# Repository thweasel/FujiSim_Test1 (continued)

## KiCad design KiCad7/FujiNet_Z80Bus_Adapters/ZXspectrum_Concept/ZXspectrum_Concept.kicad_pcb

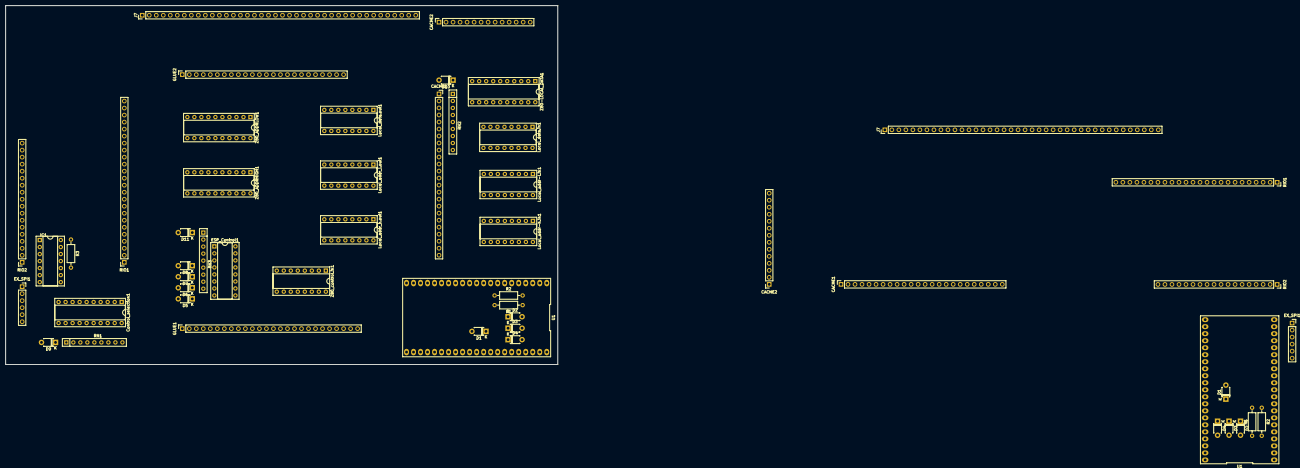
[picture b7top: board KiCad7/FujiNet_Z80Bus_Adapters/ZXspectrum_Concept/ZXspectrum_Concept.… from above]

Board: 2 copper layers, 200.0 x 130.0 mm, 52 parts (0 on the bottom side), 130 nets, no tracks yet.

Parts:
CACHE1, CACHE1#2: Conn_01x24_Socket; PinSocket_1x24_P2.54mm_Vertical
CACHE2, CACHE2#2: Conn_01x14_Socket; PinSocket_1x14_P2.54mm_Vertical
Control_selection1: 74HC244N; DIP-20_W7.62mm_Socket
D1, D1#2, D2, D2#2, D3, D3#2, D4, D4#2, D5, D6, D7, D8, D9, D10, D11: 1N4148; D_T-1_P5.08mm_Horizontal
ESP_Control1: 74595N; DIP-16_W7.62mm_Socket
EX_SPI1, EX_SPI1#2: PinSocket_2.54mm; PinSocket_1x06_P2.54mm_Vertical
GLUE1: Conn_01x26_Socket; PinSocket_1x26_P2.54mm_Vertical
GLUE2: Conn_01x24_Socket; PinSocket_1x24_P2.54mm_Vertical
IC1: 74HC32N; DIP-14_W7.62mm_Socket
J7, J7#2: DIAG-HOST_SYSTEM_BUS; PinHeader_1x40_P2.54mm_Vertical
Local_addr-h.in1: 74HC165N; DIP-16_W7.62mm_Socket
Local_addr-l.in1: 74HC165N; DIP-16_W7.62mm_Socket
Local_addr_h.out1: 74595N; DIP-16_W7.62mm_Socket
Local_addr_l.out1: 74595N; DIP-16_W7.62mm_Socket
Local_data.in1: 74HC165N; DIP-16_W7.62mm_Socket
Local_data.out1: 74595N; DIP-16_W7.62mm_Socket
R1, R1#2, R2, R2#2, R3: 22K; R_Axial_DIN0207_L6.3mm_D2.5mm_P10.16mm_Horizontal
RIO1, RIO1#2: Conn_01x24_Socket; PinSocket_1x24_P2.54mm_Vertical
RIO2, RIO2#2: Conn_01x18_Socket; PinSocket_1x18_P2.54mm_Vertical
RN1: LOCAL_CONTROL_BIAS; R_Array_SIP9
RN2, RN3: 4609M-101-103LF; R_Array_SIP9
U1, U1#2: FREENOVE_ESP32-WROVER-DEV
Z80-LOCAL_DATA1, Z80_ADDRHIGH1, Z80_ADDRLOW1: 74HC245N; DIP-20_W7.62mm_Socket
Z80_control.in1: 74HC165N; DIP-16_W7.62mm_Socket

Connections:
+5V: CACHE2.1, CACHE2#2.1, Control_selection1.20 (VCC), D9.2 (A), D10.2 (A), D11.2 (A), ESP_Control1.16 (VCC), EX_SPI1.5, GLUE1.1, IC1.14 (VCC), Local_addr-h.in1.16 (VCC), Local_addr-l.in1.16 (VCC), Local_addr_h.out1.16 (VCC), Local_addr_l.out1.16 (VCC), Local_data.in1.16 (VCC), Local_data.out1.16 (VCC), R1.2, R1#2.2, R3.1, RIO2.1, RIO2#2.1, U1.20 (+5V), U1#2.20 (+5V), Z80-LOCAL_DATA1.20 (VCC), Z80_ADDRHIGH1.20 (VCC), Z80_ADDRLOW1.20 (VCC), Z80_control.in1.16 (VCC)
/CACHE connector/CACHE_CONTROL.A16: CACHE2.2, CACHE2#2.2, GLUE2.14
/CACHE connector/CACHE_CONTROL.CS: CACHE2.5, CACHE2#2.5, GLUE2.17
/CACHE connector/CACHE_CONTROL.DATASTATUS+PERM_Z80_IORQ: CACHE2.6, CACHE2#2.6, GLUE2.13
/CACHE connector/CACHE_CONTROL.OE: CACHE2.4, CACHE2#2.4, GLUE2.16
/CACHE connector/CACHE_CONTROL.WE: CACHE2.3, CACHE2#2.3, GLUE2.15
/CACHE connector/CACHE_DATASTATUS: CACHE2.12, CACHE2#2.12, GLUE2.5, RIO2.13, RIO2#2.13
/CACHE connector/CACHE_SEL_0: CACHE2.8, CACHE2#2.8, RIO2.9, RIO2#2.9
/CACHE connector/CACHE_SEL_1: CACHE2.9, CACHE2#2.9, RIO2.10, RIO2#2.10
/CACHE connector/CACHE_SEL_2: CACHE2.10, CACHE2#2.10, RIO2.11, RIO2#2.11
/CACHE connector/CACHE_SEL_3: CACHE2.11, CACHE2#2.11, RIO2.12, RIO2#2.12
/CACHE connector/LOCAL_A0: CACHE1.9, CACHE1#2.9, Local_addr-l.in1.11 (D0), Local_addr_l.out1.15 (QA), Z80_ADDRLOW1.18 (B0)
/CACHE connector/LOCAL_A1: CACHE1.10, CACHE1#2.10, Local_addr-l.in1.12 (D1), Local_addr_l.out1.1 (QB), Z80_ADDRLOW1.17 (B1)
/CACHE connector/LOCAL_A2: CACHE1.11, CACHE1#2.11, Local_addr-l.in1.13 (D2), Local_addr_l.out1.2 (QC), Z80_ADDRLOW1.16 (B2)
/CACHE connector/LOCAL_A3: CACHE1.12, CACHE1#2.12, Local_addr-l.in1.14 (D3), Local_addr_l.out1.3 (QD), Z80_ADDRLOW1.15 (B3)
/CACHE connector/LOCAL_A4: CACHE1.13, CACHE1#2.13, Local_addr-l.in1.3 (D4), Local_addr_l.out1.4 (QE), Z80_ADDRLOW1.14 (B4)
/CACHE connector/LOCAL_A5: CACHE1.14, CACHE1#2.14, Local_addr-l.in1.4 (D5), Local_addr_l.out1.5 (QF), Z80_ADDRLOW1.13 (B5)
/CACHE connector/LOCAL_A6: CACHE1.15, CACHE1#2.15, Local_addr-l.in1.5 (D6), Local_addr_l.out1.6 (QG), Z80_ADDRLOW1.12 (B6)
/CACHE connector/LOCAL_A7: CACHE1.16, CACHE1#2.16, Local_addr-l.in1.6 (D7), Local_addr_l.out1.7 (QH), Z80_ADDRLOW1.11 (B7)
/CACHE connector/LOCAL_A8: CACHE1.17, CACHE1#2.17, Local_addr-h.in1.11 (D0), Local_addr_h.out1.15 (QA), Z80_ADDRHIGH1.18 (B0)
/CACHE connector/LOCAL_A9: CACHE1.18, CACHE1#2.18, Local_addr-h.in1.12 (D1), Local_addr_h.out1.1 (QB), Z80_ADDRHIGH1.17 (B1)
/CACHE connector/LOCAL_A10: CACHE1.19, CACHE1#2.19, Local_addr-h.in1.13 (D2), Local_addr_h.out1.2 (QC), Z80_ADDRHIGH1.16 (B2)
/CACHE connector/LOCAL_A11: CACHE1.20, CACHE1#2.20, Local_addr-h.in1.14 (D3), Local_addr_h.out1.3 (QD), Z80_ADDRHIGH1.15 (B3)
/CACHE connector/LOCAL_A12: CACHE1.21, CACHE1#2.21, Local_addr-h.in1.3 (D4), Local_addr_h.out1.4 (QE), Z80_ADDRHIGH1.14 (B4)
/CACHE connector/LOCAL_A13: CACHE1.22, CACHE1#2.22, Local_addr-h.in1.4 (D5), Local_addr_h.out1.5 (QF), Z80_ADDRHIGH1.13 (B5)
/CACHE connector/LOCAL_A14: CACHE1.23, CACHE1#2.23, Local_addr-h.in1.5 (D6), Local_addr_h.out1.6 (QG), Z80_ADDRHIGH1.12 (B6)
/CACHE connector/LOCAL_A15: CACHE1.24, CACHE1#2.24, Local_addr-h.in1.6 (D7), Local_addr_h.out1.7 (QH), Z80_ADDRHIGH1.11 (B7)
/CACHE connector/LOCAL_D0: CACHE1.1, CACHE1#2.1, Local_data.in1.11 (D0), Local_data.out1.15 (QA), RN2.2 (R1), Z80-LOCAL_DATA1.18 (B0)
/CACHE connector/LOCAL_D1: CACHE1.2, CACHE1#2.2, Local_data.in1.12 (D1), Local_data.out1.1 (QB), RN2.3 (R2), Z80-LOCAL_DATA1.17 (B1)
/CACHE connector/LOCAL_D2: CACHE1.3, CACHE1#2.3, Local_data.in1.13 (D2), Local_data.out1.2 (QC), RN2.4 (R3), Z80-LOCAL_DATA1.16 (B2)
/CACHE connector/LOCAL_D3: CACHE1.4, CACHE1#2.4, Local_data.in1.14 (D3), Local_data.out1.3 (QD), RN2.5 (R4), Z80-LOCAL_DATA1.15 (B3)
/CACHE connector/LOCAL_D4: CACHE1.5, CACHE1#2.5, Local_data.in1.3 (D4), Local_data.out1.4 (QE), RN2.6 (R5), Z80-LOCAL_DATA1.14 (B4)
/CACHE connector/LOCAL_D5: CACHE1.6, CACHE1#2.6, Local_data.in1.4 (D5), Local_data.out1.5 (QF), RN2.7 (R6), Z80-LOCAL_DATA1.13 (B5)
/CACHE connector/LOCAL_D6: CACHE1.7, CACHE1#2.7, Local_data.in1.5 (D6), Local_data.out1.6 (QG), RN2.8 (R7), Z80-LOCAL_DATA1.12 (B6)
/CACHE connector/LOCAL_D7: CACHE1.8, CACHE1#2.8, Local_data.in1.6 (D7), Local_data.out1.7 (QH), RN2.9 (R8), Z80-LOCAL_DATA1.11 (B7)
/CACHE connector/Z80_HARDLOCK: CACHE2.7, CACHE2#2.7, GLUE1.22, U1.4 (GPIO39), U1#2.4 (GPIO39)
/CORE/ESP_HARDLOCK: GLUE1.20, U1.26 (GPIO2), U1#2.26 (GPIO2)
/CORE/ESP_INT: D2.2 (A), D2#2.2 (A), D3.2 (A), D3#2.2 (A), D4.2 (A), D4#2.2 (A), R1.1, R1#2.1, R2.2, R2#2.2, U1.3 (GPIO36), U1#2.3 (GPIO36)
/CORE/ESP_PULSE: IC1.1, U1.11 (GPIO27), U1#2.11 (GPIO27)
/CORE/ESP_ROMSEL_0: GLUE1.18, U1.23 (GPIO7), U1#2.23 (GPIO7)
/CORE/ESP_ROMSEL_1: GLUE1.19, U1.22 (GPIO6), U1#2.22 (GPIO6)
/CORE/ESP_ROM_WR_PROTECT: GLUE1.17, U1.28 (GPIO4), U1#2.28 (GPIO4)
/CORE/ESP_SPI_INT.CE: Local_addr-h.in1.15 (~CE), Local_addr-l.in1.15 (~CE), Local_data.in1.15 (~CE), U1.31 (GPIO5), U1#2.31 (GPIO5), Z80_control.in1.15 (~CE)
/CORE/ESP_SPI_INT.MISO: Local_addr-h.in1.7 (~Q7), U1.33 (GPIO19), U1#2.33 (GPIO19)
/CORE/ESP_SPI_INT.MOSI: Local_data.out1.14 (SER), U1.39 (GPIO23), U1#2.39 (GPIO23)
/CORE/ESP_SPI_INT.MR: ESP_Control1.10 (~SRCLR), Local_addr_h.out1.10 (~SRCLR), Local_addr_l.out1.10 (~SRCLR), Local_data.out1.10 (~SRCLR), R3.2
/CORE/ESP_SPI_INT.OE: ESP_Control1.13 (~OE), Local_addr_h.out1.13 (~OE), Local_addr_l.out1.13 (~OE), U1.8 (GPIO33), U1#2.8 (GPIO33)
/CORE/ESP_SPI_INT.PL: Local_addr-h.in1.1 (~PL), Local_addr-l.in1.1 (~PL), Local_data.in1.1 (~PL), U1.9 (GPIO25), U1#2.9 (GPIO25), Z80_control.in1.1 (~PL)
/CORE/ESP_SPI_INT.SCK: ESP_Control1.11 (SRCLK), Local_addr-h.in1.2 (CP), Local_addr-l.in1.2 (CP), Local_addr_h.out1.11 (SRCLK), Local_addr_l.out1.11 (SRCLK), Local_data.in1.2 (CP), Local_data.out1.11 (SRCLK), U1.32 (GPIO18), U1#2.32 (GPIO18), Z80_control.in1.2 (CP)
/CORE/ESP_SPI_INT.STC: ESP_Control1.12 (RCLK), Local_addr_h.out1.12 (RCLK), Local_addr_l.out1.12 (RCLK), Local_data.out1.12 (RCLK), U1.10 (GPIO26), U1#2.10 (GPIO26)
/CORE/ESP_WAIT_RESET: GLUE2.6, U1.18 (GPIO11), U1#2.18 (GPIO11)
/CORE/EX_MISO: EX_SPI1.3, U1.13 (GPIO12), U1#2.13 (GPIO12)
/CORE/EX_MOSI: EX_SPI1.4, U1.15 (GPIO13), U1#2.15 (GPIO13)
/CORE/EX_SCK: EX_SPI1.2, U1.12 (GPIO14), U1#2.12 (GPIO14)
/CORE/EX_SS: EX_SPI1.1, U1.25 (GPIO8), U1#2.25 (GPIO8)
/CORE/SD_CARD_SS: U1.24 (GPIO15), U1.38 (GPIO22), U1#2.24 (GPIO15), U1#2.38 (GPIO22)
/CORE/Z80_HARDLOCK_RESET: D3.1 (K), D3#2.1 (K), GLUE2.3, RIO2.15, RIO2#2.15
/GLUE connector/!ESP_HARDLOCK: Control_selection1.19 (2OE), GLUE1.21
/GLUE connector/PERM_Z80_IORQ: GLUE1.24, RIO2.17, RIO2#2.17
/GLUE connector/RIO_CONTROL.A14: GLUE2.20, RIO2.4, RIO2#2.4
/GLUE connector/RIO_CONTROL.A15: GLUE2.19, RIO2.3, RIO2#2.3
/GLUE connector/RIO_CONTROL.A16: GLUE2.18, RIO2.2, RIO2#2.2
/GLUE connector/RIO_CONTROL.CE: GLUE2.23, RIO2.6, RIO2#2.6
/GLUE connector/RIO_CONTROL.OE: GLUE2.22, RIO2.7, RIO2#2.7
/GLUE connector/RIO_CONTROL.ROM_RDY: GLUE2.24, RIO2.8, RIO2#2.8
/GLUE connector/RIO_CONTROL.WE: GLUE2.21, RIO2.5, RIO2#2.5
/GLUE connector/WAIT_IO: GLUE2.4, RIO2.14, RIO2#2.14
/GLUE connector/Z80_BUS_CONTROL.Z80_ADD_DIR: GLUE2.10, Z80_ADDRHIGH1.1 (A->B), Z80_ADDRLOW1.1 (A->B)
/GLUE connector/Z80_BUS_CONTROL.Z80_ADD_OE: GLUE2.9, Z80_ADDRHIGH1.19 (CE), Z80_ADDRLOW1.19 (CE)
/GLUE connector/Z80_BUS_CONTROL.Z80_DATA_DIR: GLUE2.11, Z80-LOCAL_DATA1.1 (A->B)
/GLUE connector/Z80_BUS_CONTROL.Z80_DATA_OE: GLUE2.12, Z80-LOCAL_DATA1.19 (CE)
/GLUE connector/Z80_HARDLOCK_SET: GLUE2.2, RIO2.16, RIO2#2.16
/RIO connector/Z80_A0: GLUE2.1, J7#2.18, RIO1.9, RIO1#2.9, Z80_ADDRLOW1.2 (A0)
/RIO connector/Z80_A1: J7#2.17, RIO1.10, RIO1#2.10, Z80_ADDRLOW1.3 (A1)
/RIO connector/Z80_A2: J7#2.16, RIO1.11, RIO1#2.11, Z80_ADDRLOW1.4 (A2)
/RIO connector/Z80_A3: J7#2.15, RIO1.12, RIO1#2.12, Z80_ADDRLOW1.5 (A3)
/RIO connector/Z80_A4: J7#2.14, RIO1.13, RIO1#2.13, Z80_ADDRLOW1.6 (A4)
/RIO connector/Z80_A5: J7#2.13, RIO1.14, RIO1#2.14, Z80_ADDRLOW1.7 (A5)
/RIO connector/Z80_A6: J7#2.12, RIO1.15, RIO1#2.15, Z80_ADDRLOW1.8 (A6)
/RIO connector/Z80_A7: J7#2.11, RIO1.16, RIO1#2.16, Z80_ADDRLOW1.9 (A7)
/RIO connector/Z80_A8: J7#2.26, RIO1.17, RIO1#2.17, Z80_ADDRHIGH1.2 (A0)
/RIO connector/Z80_A9: J7#2.25, RIO1.18, RIO1#2.18, Z80_ADDRHIGH1.3 (A1)
/RIO connector/Z80_A10: J7#2.24, RIO1.19, RIO1#2.19, Z80_ADDRHIGH1.4 (A2)
/RIO connector/Z80_A11: J7#2.23, RIO1.20, RIO1#2.20, Z80_ADDRHIGH1.5 (A3)
/RIO connector/Z80_A12: J7#2.22, RIO1.21, RIO1#2.21, Z80_ADDRHIGH1.6 (A4)
/RIO connector/Z80_A13: J7#2.21, RIO1.22, RIO1#2.22, Z80_ADDRHIGH1.7 (A5)
/RIO connector/Z80_A14: GLUE2.7, J7#2.20, RIO1.23, RIO1#2.23, Z80_ADDRHIGH1.8 (A6)
/RIO connector/Z80_A15: GLUE2.8, J7#2.19, RIO1.24, RIO1#2.24, Z80_ADDRHIGH1.9 (A7)
/RIO connector/Z80_D0: J7#2.34, RIO1.1, RIO1#2.1, Z80-LOCAL_DATA1.2 (A0)
/RIO connector/Z80_D1: J7#2.33, RIO1.2, RIO1#2.2, Z80-LOCAL_DATA1.3 (A1)
/RIO connector/Z80_D2: J7#2.32, RIO1.3, RIO1#2.3, Z80-LOCAL_DATA1.4 (A2)
/RIO connector/Z80_D3: J7#2.31, RIO1.4, RIO1#2.4, Z80-LOCAL_DATA1.5 (A3)
/RIO connector/Z80_D4: J7#2.30, RIO1.5, RIO1#2.5, Z80-LOCAL_DATA1.6 (A4)
/RIO connector/Z80_D5: J7#2.29, RIO1.6, RIO1#2.6, Z80-LOCAL_DATA1.7 (A5)
/RIO connector/Z80_D6: J7#2.28, RIO1.7, RIO1#2.7, Z80-LOCAL_DATA1.8 (A6)
/RIO connector/Z80_D7: J7#2.27, RIO1.8, RIO1#2.8, Z80-LOCAL_DATA1.9 (A7)
/SPI/ESP_CONTROL.BUSRQ: Control_selection1.1 (1OE), D8.1 (K), ESP_Control1.4 (QE), GLUE1.15, RN3.6 (R5)
/SPI/ESP_CONTROL.IORQ: Control_selection1.6 (1A2), Control_selection1.13 (2A2), ESP_Control1.2 (QC), GLUE1.13, RN3.4 (R3)
/SPI/ESP_CONTROL.MEMRQ: Control_selection1.8 (1A3), Control_selection1.11 (2A3), ESP_Control1.3 (QD), GLUE1.14, RN3.5 (R4)
/SPI/ESP_CONTROL.NMI: D5.1 (K), ESP_Control1.7 (QH), RN3.9 (R8)
/SPI/ESP_CONTROL.RD: Control_selection1.2 (1A0), Control_selection1.17 (2A0), ESP_Control1.15 (QA), RN3.2 (R1)
/SPI/ESP_CONTROL.ROMCS: D6.1 (K), ESP_Control1.6 (QG), GLUE1.16, RN3.8 (R7)
/SPI/ESP_CONTROL.WAIT: D7.1 (K), ESP_Control1.5 (QF), RN3.7 (R6)
/SPI/ESP_CONTROL.WR: ESP_Control1.1 (QB), GLUE1.12, IC1.2, Local_data.out1.13 (~OE), RN3.3 (R2)
/SPI/ESP_CONTROL.WR+ESP_PULSE: Control_selection1.4 (1A1), Control_selection1.15 (2A1), IC1.3
/SPI/LOCAL_CONTROL.IORQ: Control_selection1.14 (1Y2), GLUE1.10, RN1.3 (R2)
/SPI/LOCAL_CONTROL.MEMRQ: Control_selection1.12 (1Y3), GLUE1.11, RN1.2 (R1)
/SPI/LOCAL_CONTROL.RD: Control_selection1.18 (1Y0), GLUE1.8, RN1.5 (R4)
/SPI/LOCAL_CONTROL.WR: Control_selection1.16 (1Y1), GLUE1.9, RN1.4 (R3)
/SPI/Z80_CONTROL.BUSACK: D4.1 (K), D4#2.1 (K), J7#2.9, Z80_control.in1.5 (D6)
/SPI/Z80_CONTROL.BUSRQ: D8.2 (A), GLUE1.6, J7#2.5, Z80_control.in1.3 (D4)
/SPI/Z80_CONTROL.IORQ: Control_selection1.7 (2Y2), GLUE1.4, J7#2.3, Z80_control.in1.13 (D2)
/SPI/Z80_CONTROL.MEMRQ: Control_selection1.9 (2Y3), GLUE1.5, J7#2.4, Z80_control.in1.14 (D3)
/SPI/Z80_CONTROL.NMI: D5.2 (A), J7#2.7, Z80_control.in1.6 (D7)
/SPI/Z80_CONTROL.RD: Control_selection1.3 (2Y0), GLUE1.2, J7#2.1, Z80_control.in1.11 (D0)
/SPI/Z80_CONTROL.RESET: D1.2 (A), D1#2.2 (A), J7#2.10
/SPI/Z80_CONTROL.ROMCS: D6.2 (A), J7#2.8
/SPI/Z80_CONTROL.WAIT: D2.1 (K), D2#2.1 (K), D7.2 (A), GLUE1.7, J7#2.6, Z80_control.in1.4 (D5)
/SPI/Z80_CONTROL.WR: Control_selection1.5 (2Y1), GLUE1.3, J7#2.2, Z80_control.in1.12 (D1)
GND: CACHE2.14, CACHE2#2.14, Control_selection1.10 (GND), ESP_Control1.8 (GND), EX_SPI1.6, GLUE1.26, IC1.4, IC1.5, IC1.7 (GND), IC1.9, IC1.10, IC1.12, IC1.13, J7#2.40, Local_addr-h.in1.8 (GND), Local_addr-l.in1.8 (GND), Local_addr_h.out1.8 (GND), Local_addr_l.out1.8 (GND), Local_data.in1.8 (GND), Local_data.in1.10 (DS), Local_data.out1.8 (GND), R2.1, R2#2.1, RIO2.18, RIO2#2.18, U1.21 (GND), U1.34 (GND), U1.40 (GND), U1#2.21 (GND), U1#2.34 (GND), U1#2.40 (GND), Z80-LOCAL_DATA1.10 (GND), Z80_ADDRHIGH1.10 (GND), Z80_ADDRLOW1.10 (GND), Z80_control.in1.8 (GND)
unnamed: D1.1 (K), D1#2.1 (K), U1.35 (GPIO21), U1#2.35 (GPIO21)
unnamed: D9.1 (K), RN1.1 (common)
unnamed: D10.1 (K), RN2.1 (common)
unnamed: D11.1 (K), RN3.1 (common)
unnamed: ESP_Control1.9 (QH'), Local_addr_l.out1.14 (SER)
unnamed: ESP_Control1.14 (SER), Local_data.out1.9 (QH')
unnamed: Local_addr-h.in1.10 (DS), Local_addr-l.in1.7 (~Q7)
unnamed: Local_addr-l.in1.10 (DS), Z80_control.in1.7 (~Q7)
unnamed: Local_addr_h.out1.14 (SER), Local_addr_l.out1.9 (QH')
unnamed: Local_data.in1.7 (~Q7), Z80_control.in1.10 (DS)

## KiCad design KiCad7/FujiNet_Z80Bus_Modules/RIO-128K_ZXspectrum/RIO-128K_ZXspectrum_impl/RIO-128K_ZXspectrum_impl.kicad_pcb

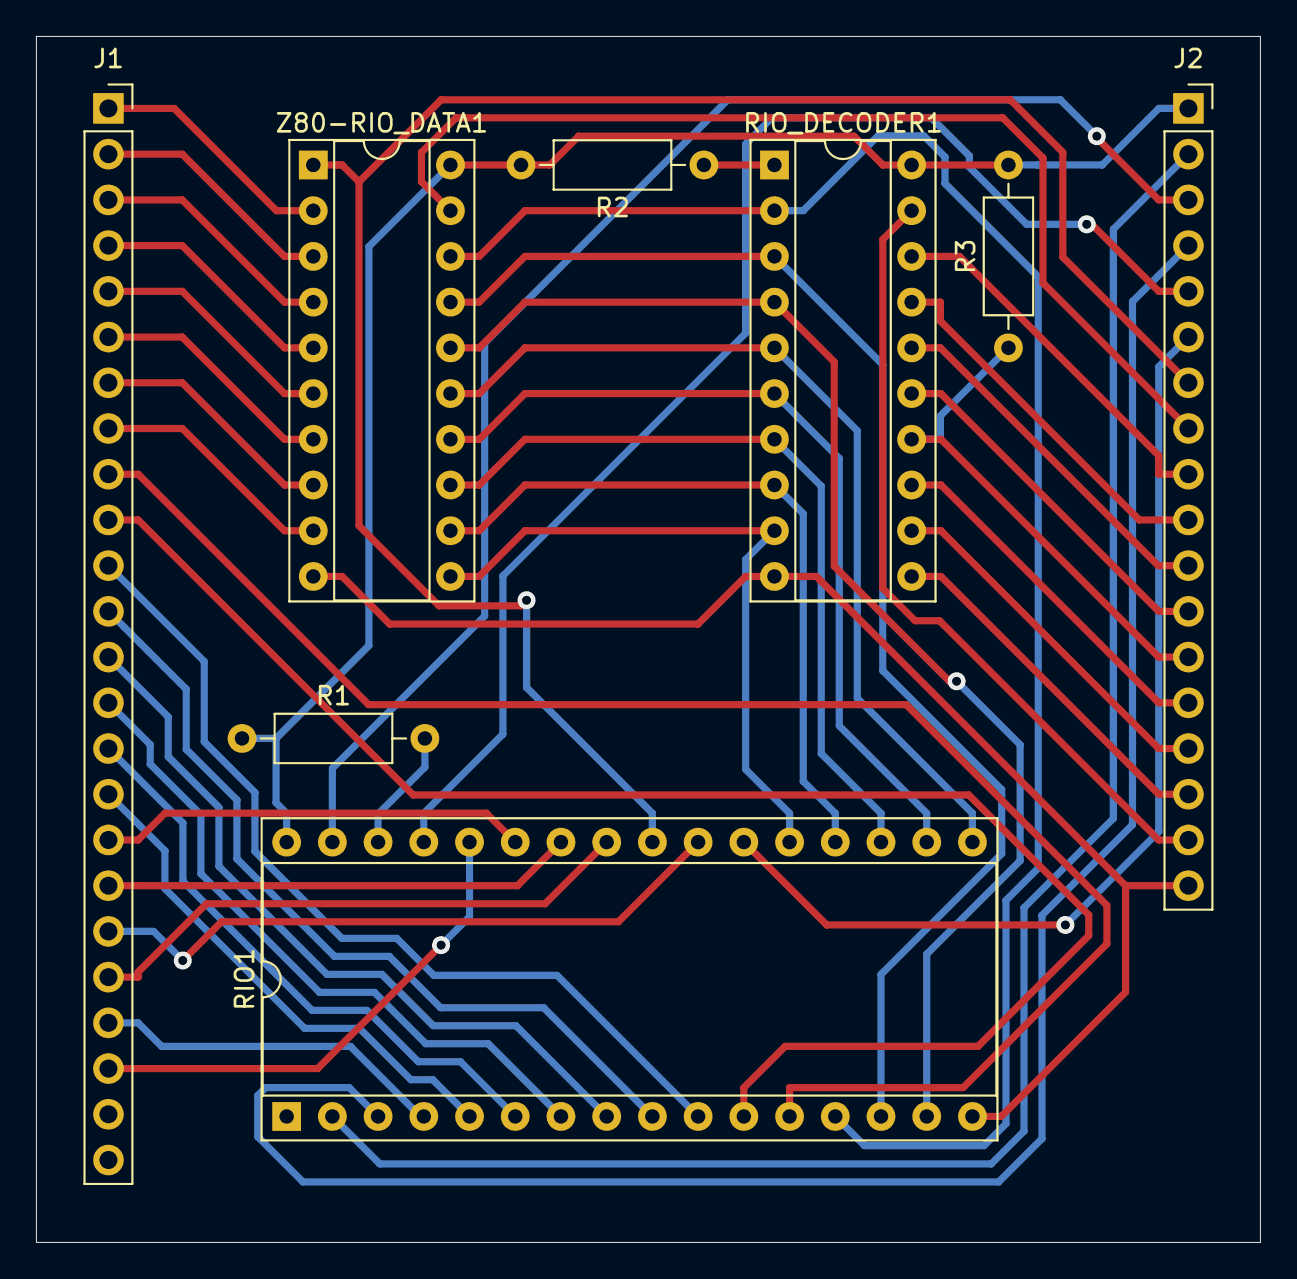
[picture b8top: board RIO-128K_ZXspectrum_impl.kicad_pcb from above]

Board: 2 copper layers, 68.0 x 67.0 mm, 8 parts (0 on the bottom side), 50 nets.

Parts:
J1: Conn_01x24_Socket; PinSocket_1x24_P2.54mm_Vertical
J2: Conn_01x18_Socket; PinSocket_1x18_P2.54mm_Vertical
R1, R2, R3: 10K; R_Axial_DIN0207_L6.3mm_D2.5mm_P10.16mm_Horizontal
RIO1: AS6C1008-55PCN; DIP-32_W15.24mm_Socket
RIO_DECODER1: 74HC245N; DIP-20_W7.62mm_Socket
Z80-RIO_DATA1: 74HC245N; DIP-20_W7.62mm_Socket

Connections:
+5V: J2.1, R1.1, R2.2, R3.2, RIO1.32 (VCC), RIO_DECODER1.20 (VCC), Z80-RIO_DATA1.20 (VCC)
/RIO-128K_ZXspectrum/CACHE_DATASTATUS: J2.13, R3.1, RIO_DECODER1.14 (B4)
/RIO-128K_ZXspectrum/CACHE_SEL_0: J2.9, RIO_DECODER1.18 (B0)
/RIO-128K_ZXspectrum/CACHE_SEL_1: J2.10, RIO_DECODER1.17 (B1)
/RIO-128K_ZXspectrum/CACHE_SEL_2: J2.11, RIO_DECODER1.16 (B2)
/RIO-128K_ZXspectrum/CACHE_SEL_3: J2.12, RIO_DECODER1.15 (B3)
/RIO-128K_ZXspectrum/PERM_Z80_IORQ: J2.17, RIO_DECODER1.19 (CE)
/RIO-128K_ZXspectrum/RIO_CE2: R1.2, RIO1.30 (CE2#)
/RIO-128K_ZXspectrum/RIO_CONTROL.A14: J2.4, RIO1.3 (A14)
/RIO-128K_ZXspectrum/RIO_CONTROL.A15: J2.3, RIO1.31 (A15)
/RIO-128K_ZXspectrum/RIO_CONTROL.A16: J2.2, RIO1.2 (A16)
/RIO-128K_ZXspectrum/RIO_CONTROL.CE: J2.6, RIO1.22 (CE#)
/RIO-128K_ZXspectrum/RIO_CONTROL.OE: J2.7, RIO1.24 (OE#), Z80-RIO_DATA1.1 (A->B)
/RIO-128K_ZXspectrum/RIO_CONTROL.ROM_RDY: J2.8, Z80-RIO_DATA1.19 (CE)
/RIO-128K_ZXspectrum/RIO_CONTROL.WE: J2.5, RIO1.29 (WE#)
/RIO-128K_ZXspectrum/ROM_D0: RIO1.13 (DQ0), RIO_DECODER1.2 (A0), Z80-RIO_DATA1.18 (B0)
/RIO-128K_ZXspectrum/ROM_D1: RIO1.14 (DQ1), RIO_DECODER1.3 (A1), Z80-RIO_DATA1.17 (B1)
/RIO-128K_ZXspectrum/ROM_D2: RIO1.15 (DQ2), RIO_DECODER1.4 (A2), Z80-RIO_DATA1.16 (B2)
/RIO-128K_ZXspectrum/ROM_D3: RIO1.17 (DQ3), RIO_DECODER1.5 (A3), Z80-RIO_DATA1.15 (B3)
/RIO-128K_ZXspectrum/ROM_D4: RIO1.18 (DQ4), RIO_DECODER1.6 (A4), Z80-RIO_DATA1.14 (B4)
/RIO-128K_ZXspectrum/ROM_D5: RIO1.19 (DQ5), RIO_DECODER1.7 (A5), Z80-RIO_DATA1.13 (B5)
/RIO-128K_ZXspectrum/ROM_D6: RIO1.20 (DQ6), RIO_DECODER1.8 (A6), Z80-RIO_DATA1.12 (B6)
/RIO-128K_ZXspectrum/ROM_D7: RIO1.21 (DQ7), RIO_DECODER1.9 (A7), Z80-RIO_DATA1.11 (B7)
/RIO-128K_ZXspectrum/WAIT_IO: J2.14, RIO_DECODER1.13 (B5)
/RIO-128K_ZXspectrum/Z80_A0: J1.9, RIO1.12 (A0)
/RIO-128K_ZXspectrum/Z80_A1: J1.10, RIO1.11 (A1)
/RIO-128K_ZXspectrum/Z80_A2: J1.11, RIO1.10 (A2)
/RIO-128K_ZXspectrum/Z80_A3: J1.12, RIO1.9 (A3)
/RIO-128K_ZXspectrum/Z80_A4: J1.13, RIO1.8 (A4)
/RIO-128K_ZXspectrum/Z80_A5: J1.14, RIO1.7 (A5)
/RIO-128K_ZXspectrum/Z80_A6: J1.15, RIO1.6 (A6)
/RIO-128K_ZXspectrum/Z80_A7: J1.16, RIO1.5 (A7)
/RIO-128K_ZXspectrum/Z80_A8: J1.17, RIO1.27 (A8)
/RIO-128K_ZXspectrum/Z80_A9: J1.18, RIO1.26 (A9)
/RIO-128K_ZXspectrum/Z80_A10: J1.19, RIO1.23 (A10)
/RIO-128K_ZXspectrum/Z80_A11: J1.20, RIO1.25 (A11)
/RIO-128K_ZXspectrum/Z80_A12: J1.21, RIO1.4 (A12)
/RIO-128K_ZXspectrum/Z80_A13: J1.22, RIO1.28 (A13)
/RIO-128K_ZXspectrum/Z80_D0: J1.1, Z80-RIO_DATA1.2 (A0)
/RIO-128K_ZXspectrum/Z80_D1: J1.2, Z80-RIO_DATA1.3 (A1)
/RIO-128K_ZXspectrum/Z80_D2: J1.3, Z80-RIO_DATA1.4 (A2)
/RIO-128K_ZXspectrum/Z80_D3: J1.4, Z80-RIO_DATA1.5 (A3)
/RIO-128K_ZXspectrum/Z80_D4: J1.5, Z80-RIO_DATA1.6 (A4)
/RIO-128K_ZXspectrum/Z80_D5: J1.6, Z80-RIO_DATA1.7 (A5)
/RIO-128K_ZXspectrum/Z80_D6: J1.7, Z80-RIO_DATA1.8 (A6)
/RIO-128K_ZXspectrum/Z80_D7: J1.8, Z80-RIO_DATA1.9 (A7)
/RIO-128K_ZXspectrum/Z80_HARDLOCK_RESET: J2.15, RIO_DECODER1.12 (B6)
/RIO-128K_ZXspectrum/Z80_HARDLOCK_SET: J2.16, RIO_DECODER1.11 (B7)
GND: J2.18, RIO1.16 (VSS), RIO_DECODER1.10 (GND), Z80-RIO_DATA1.10 (GND)
unnamed: R2.1, RIO_DECODER1.1 (A->B)

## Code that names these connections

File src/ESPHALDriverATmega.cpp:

#include <ESPHALDriverATmega.h>
#include "consoleDebug.h"

#define DEBUG_SPI_READ false
#define DEBUG_SPI_WRITE false
#define DEBUG_SPI_FORMAT HEX // BIN / HEX /DEC



#define RUNSLOW false
#define SLOWTIME 100
#define SLOWPULSEDIV 5



//void transfer(void *buf, size_t count)

//
// PIN Map


// ARDUINO SPI PINS
// SPI SS   53
// SPI SCK  52
// SPI MOSI 51
// SPI MISO 50

#define SS_START LOW
#define SS_STOP HIGH


#define ESP_SPI_INT_STC 49  // OUTPUT (pulse)     --SPI Latch Bus packet in shift registers for output
#define ESP_SPI_INT_OE 48   // OUTPUT (send/stop) --SPI Enable Output of an Address from shift registers
#define ESP_PULSE 47        // OUTPUT (pulse)     -- Generate a pulse for Writing
#define ESP_SPI_INT_PL 46   // OUTPUT (pulse)     -- SPI Load Host BUS state to shift registers
#define ESP_SPI_INT_CE 41   // OUTPUT


#define ESP_RIO_PROTECT 5   // OUTPUT (enable/disable)
#define ESP_RESET 6         // OUTPUT LOW RESETS HOST
#define ESP_INT 3           // INPUT  [INTERRUPT]

#define ESP_WAIT_RESET 8    // OUTPUT (pulse)
#define Z80_HARDLOCK 9      // INPUT  (get)
#define ESP_HARDLOCK 10     // OUTPUT (set/release)
#define ESP_ROMSELECT0 11   // OUTPUT (select ROM)
#define ESP_ROMSELECT1 12   // OUTPUT (select ROM)


//
// BUS BusPacketBuffer

/* 
  BUS PACKET BYTES
    BusPacketBuffer[3] = Data;
    BusPacketBuffer[2] = Control;
    BusPacketBuffer[1] = loAddr;
    BusPacketBuffer[0] = hiAddr;
*/

uint8_t BusPacketBuffer[4]; 

void clearBusPacketBuffer (void)
{
  BusPacketBuffer[3] = 0xFF; // Data
  BusPacketBuffer[2] = 0xFF; // Control
  BusPacketBuffer[1] = 0xFF; // LoAddr
  BusPacketBuffer[0] = 0xFF; // HiAddr
}

uint8_t * setBusPacketBuffer (uint8_t Data, uint8_t Control, uint16_t Address)
{

  uint8_t loAddr = (uint8_t)(Address);
  uint8_t hiAddr = (uint8_t)(Address >> 8);

  BusPacketBuffer[3] = Data;
  BusPacketBuffer[2] = Control;
  BusPacketBuffer[1] = loAddr;
  BusPacketBuffer[0] = hiAddr;

  return BusPacketBuffer;
}

//
// SPI BUS hardware implementation


SPISettings myTXSpiSettings (100000,MSBFIRST,SPI_MODE0);
SPISettings myRXSpiSettings (100000,MSBFIRST,SPI_MODE0);  // IF clock is inverted to 165s
//SPISettings myRXSpiSettings (1000000,MSBFIRST,SPI_MODE2); // IF clock is NOT inverted to 165s
#define LATCHINGDELAY 30

// WRITE method for the bus hardware
void writeSPI(void)
{ 
  // OUTPUT 74XX595 Shift registers (x4)

  if(DEBUG_SPI_WRITE) { consoleShowBusPacketBuffer("writeSPI",BusPacketBuffer,DEBUG_SPI_FORMAT); }

  // Load TXPacket into the Shift Regs
  SPI.beginTransaction(myTXSpiSettings);
  SPI.transfer(BusPacketBuffer,4);  
  SPI.endTransaction();

  // LATCH the Shift Regs to Storage (pulse)
  digitalWrite(ESP_SPI_INT_STC, HIGH); // Move shift to storage  
  delayMicroseconds(LATCHINGDELAY);
  if(RUNSLOW) { delay(SLOWTIME); } // SLOW THE OUTPUT POINT
  digitalWrite(ESP_SPI_INT_STC, LOW);
    
  return;
}

// READ method for the bus hardware
void readSPI(void)
{ 
  // INPUT 74xx165 Shift Registers (x4)

  // LATCH data into the Shift Regs (pulse)
  digitalWrite(ESP_SPI_INT_PL, LOW);  // Parallel Load
  if(RUNSLOW) { delay(SLOWTIME); }  // SLOW THE INPUT POINT
  delayMicroseconds(LATCHINGDELAY);
  digitalWrite(ESP_SPI_INT_PL, HIGH); // Serial Shift
  
  //clearBusPacketBuffer();
  SPI.beginTransaction(myRXSpiSettings);
  SPI.transfer(BusPacketBuffer,4);  
  SPI.endTransaction(); 
  
  // Needed if Shift registers are chained using !Q7
  //BusPacketBuffer[0] = ~BusPacketBuffer[0];
  //BusPacketBuffer[2] = ~BusPacketBuffer[2];

  if(DEBUG_SPI_READ) { consoleShowBusPacketBuffer("readSPI",BusPacketBuffer,DEBUG_SPI_FORMAT); }
  
  return; // results in BusPacketBuffer
}

// SPI BUS signal output controls
// The output from the 595s on the SPI bus must ONLY be activated when RIO's 245 Decoder is disabled.
// This code is likely to be replaced with a NOT gate that inverts the OE signal from RIO's 245 Decoder chip, so we can never conflict the LOCAL HIGH ADDR BYTE

void sendBusSignalsFromSPI(void)
{
  digitalWrite(ESP_SPI_INT_OE, LOW);
}

void stopBusSignalsFromSPI(void)
{
  digitalWrite(ESP_SPI_INT_OE, HIGH);
}



//
// Interface for Hardware Abstraction Layer


void Setup_ESPHALDriver(void)
{
  SPI.begin();

  // INPUT PINS
  pinMode(Z80_HARDLOCK, INPUT);
  digitalWrite(Z80_HARDLOCK, LOW); // Tri-State

  // ESP pin Config
  pinMode(ESP_SPI_INT_CE, OUTPUT);
  pinMode(ESP_SPI_INT_STC, OUTPUT);
  pinMode(ESP_SPI_INT_OE, OUTPUT);
  pinMode(ESP_PULSE, OUTPUT);
  pinMode(ESP_SPI_INT_PL, OUTPUT);
  pinMode(ESP_RIO_PROTECT, OUTPUT);
  pinMode(ESP_ROMSELECT0, OUTPUT);
  pinMode(ESP_ROMSELECT1, OUTPUT);
  pinMode(ESP_HARDLOCK, OUTPUT);
  pinMode(ESP_RIO_PROTECT, OUTPUT);
  pinMode(ESP_RESET, OUTPUT);

  // OUTPUT States
  digitalWrite(ESP_SPI_INT_CE, LOW);
  digitalWrite(ESP_SPI_INT_STC, HIGH);
  digitalWrite(ESP_SPI_INT_OE, HIGH);
  digitalWrite(ESP_PULSE, HIGH);
  digitalWrite(ESP_SPI_INT_PL, HIGH);
  digitalWrite(ESP_RIO_PROTECT, HIGH);  // WRITE ENABLE LOW
  digitalWrite(ESP_ROMSELECT0, LOW);
  digitalWrite(ESP_ROMSELECT1, LOW);
  digitalWrite(ESP_HARDLOCK, HIGH);     // START LOCKED
  digitalWrite(ESP_RIO_PROTECT, HIGH);  // Connect on LOW (may be buffer with NOT?)
  digitalWrite(ESP_RESET, LOW);
  return;
}


void WriteDataBUSOperation(uint8_t Data, uint8_t Control, uint16_t Address)
{
  digitalWrite(SS,SS_START);
  setBusPacketBuffer(Data,Control,Address);  
  writeSPI(); // Set Control and Address lines
  // sendBusSignalsFromSPI();  // ADDRESS BUS CONNECTED AFTER ESP HARDLOCK
  sendPulse();
  digitalWrite(SS,SS_STOP);
  return;
}

uint8_t ReadDataBUSOperation(uint8_t Control, uint16_t Address)
{ 
  digitalWrite(SS,SS_START);
  setBusPacketBuffer(0x00,Control,Address);  
  writeSPI(); // Set Control and Address lines
  // sendBusSignalsFromSPI();  // ADDRESS BUS CONNECTED AFTER ESP HARDLOCK
  readSPI();
  digitalWrite(SS,SS_STOP);
  return BusPacketBuffer[3]; // Data byte
}

uint8_t * getBUSstate(void) {
  readSPI();
  return BusPacketBuffer;
}


//
// RIO Hardware ROM/CACHE

void enableRIOProtection(void)
{
  digitalWrite(ESP_RIO_PROTECT, HIGH);
  return;
}

void disableRIOProtection(void)
{
  digitalWrite(ESP_RIO_PROTECT, LOW);
  return;
}

void setROMbank(uint8_t rom)
{
  switch (rom)
  {
  case 0:
    digitalWrite(ESP_ROMSELECT0,0);
    digitalWrite(ESP_ROMSELECT1,0);
    break;
  case 1:
    digitalWrite(ESP_ROMSELECT0,1);
    digitalWrite(ESP_ROMSELECT1,0);
    break;
  case 2:
    digitalWrite(ESP_ROMSELECT0,0);
    digitalWrite(ESP_ROMSELECT1,1);
    break;
  case 3:
    digitalWrite(ESP_ROMSELECT0,1);
    digitalWrite(ESP_ROMSELECT1,1);
    break;
  default:
    digitalWrite(ESP_ROMSELECT0,0);
    digitalWrite(ESP_ROMSELECT1,0);
    break;
  }

  return;
}


//
// OUTPUT send (Low/High)

void sendPulse(void)
{
  // Some actions need a low clock pulse to trigger
  // This pin should idel high
  digitalWrite(ESP_PULSE,LOW);
  if(RUNSLOW) { delay(SLOWTIME/SLOWPULSEDIV); }
  digitalWrite(ESP_PULSE,HIGH);
  return;
}

void sendWAITreset(void)
{
  digitalWrite(ESP_WAIT_RESET,LOW);
  if(RUNSLOW) { delay(SLOWTIME/SLOWPULSEDIV); }
  digitalWrite(ESP_WAIT_RESET,HIGH);
  return;
}

void sendRESET(void)
{
  digitalWrite(ESP_RESET,LOW);
  if(RUNSLOW) { delay(SLOWTIME/SLOWPULSEDIV); }
  delay(1); // Extend the delay as needed for clean reset of the host
  digitalWrite(ESP_RESET,HIGH);
  return;
}

//
// OUPUT set/release 

void setESPHardlock(void)       { digitalWrite(ESP_HARDLOCK,HIGH);   }
void clearESPHardlock(void)     { digitalWrite(ESP_HARDLOCK,LOW);    }


//
// INPUT get

boolean getZ80HardlockState(void) 
{ 
  if (digitalRead(Z80_HARDLOCK) == 1)
  {
    Serial.println("Z80 has lock");
    return true;
  }
  return false; 
}
boolean getINT(void)              { return !digitalRead(ESP_INT); }

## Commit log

2022-10-30 Z80 Data and Address connected
2022-10-30 Z80 IORQ WR functionality added
2022-10-30 Corrected logic on Z80 IORQ IOd CS
2022-10-30 Hardlock Triggers added
2022-10-30 z80 connect added, SPI bus fixed
2022-10-30 Z80 Cache access counter counts on RD/WR pulse
2022-10-30 Clean up on Z80 Cache Address counter
2022-10-30 House keeping on Circuit
2022-11-01 Refactoring ESP and Z80 emulation split out
2022-11-01 Z80 IO MEM RQ routines and Z80Dbus circuit debug
2022-11-01 Z80 ROM RD/WR access working
2022-11-01 Update on the IORQ address counter (working test)
2022-11-02 A14 and A15 switched between IORQ and ROMCS&MEMRQ
2022-11-02 ESP Hardlock Blocking Z80IORQ
2022-11-02 Local Data to Z80 Data gate control introduced
2022-11-06 Z80 IORQ Writes to Local Data bus
2022-11-06 Added Cache control signal logic
2022-11-08 z80 ROM and IO working
2022-11-08 Fixed the Z80 Hardlock startup conditions
2022-11-08 Scopes added to monitor z80
2022-11-08 ESP BUS connection reworked
2022-11-08 ESP IO/MEM RE/WR patterns
2022-11-09 Pull resistors added to ESP control lines
2022-11-10 Cache address counters working again
2022-11-10 Added a write pulse to enable write ops
2022-11-10 Seperation and notation updates
2022-11-10 More housekeeping and clean up (circuit)
2022-11-10 Sub circuits layed out ESPin SReg started
2022-11-12 Sketching out the BUS controls
2022-11-12 Expanded on the ESPemulation
2022-11-19 SPI in and out working
2022-11-19 Cache Status methods testing
2023-01-01 Working simulation if Simu Step 10ns
2023-01-01 ESP Local Cache chip routine test
2023-01-01 Managed to get ESP basic access to ROM/IOd
2023-01-02 circuit clean up
2023-01-02 IOd testing routine started
2023-01-02 Added minimal ESP Hardlock
2023-01-02 ESP IOd seems to be working & rw/wr decoded
2023-01-02 Start of a BUSRQ setup, needs BUSACK adding
2023-01-02 Fixed bug in ESPHardlock check
2023-01-03 Clean up circuit
2023-01-03 Circuit tunnel renaming
2023-01-03 Refactored ESP pin labels
2023-01-03 CONTROL Local/z80 >> espHLock and ESPout_BUSRQ
2023-01-03 Refactored ESPout_CONTROL_Z80/LOCAL
2023-01-03 Removed CONTROL swapped pins to ROMselect
2023-01-03 Missed some calls on Controls (builds ok)
2023-01-03 Circuit - Cache Data/Status signalling changed
2023-01-03 Circuit - ESPout CONTROL clean up
2023-01-03 Z80 control lines pulled up
2023-01-03 Z80 BUSACK added
2023-01-03 Circuit - Clean up Scopes
2023-01-03 Big clean up and move about
2023-01-03 Split z80 emulation to systeminterface
2023-01-03 Removed delays from Z80
2023-01-03 Updated Z80ROMCS
2023-01-03 ESP tests and setup refactored
2023-01-03 Refactor z80 Layers
2023-01-03 ESP Layers refactored
2023-01-03 refactored z80 test
2023-01-03 Fixed a bug in the Z80 memory ROM test
2023-01-03 Z80RQ serial output added
2023-01-03 Programmed IOd testing (failing)
2023-01-03 Flipped the ESP Lock signal
2023-01-03 Serial output for IOd testing (failing)
2023-01-03 Correction SET/RESET Z80 HARDLOCK
2023-01-04 massive bug hunt in the IOd space
2023-01-04 IOd data and status "working"
2023-01-04 Stable Version with no Z80 slowdown needed
2023-01-04 Test Serial message clean up
2023-01-04 Removed delays from the ESP test loops
2023-01-07 Workshop diagram
2023-01-07 Cache CS swaped notZ80HardLock to Z80PermittedIO
2023-01-07 WAIT based IO Lock added in
2023-01-07 ESP RESET HOST pin allocated
2023-01-07 ROMCS and ROM selection initial (Failing)
2023-01-08 D7 high added and address filter moved
2023-01-08 ROM and IOdecoder clean up
2023-01-08 More cleanup on the circuits and labels
2023-01-08 Moved about for screenshot
2023-01-11 suggested Board A allocations
2023-01-15 ESP Interrupt circuit added
2023-01-15 Added External SPI and SPI SCK control
2023-01-15 Folder structure update
2023-01-17 Clean up on Address bus gates
2023-01-18 Removed NOT gate from IOd 244 CE to A16
2023-01-19 ESP BUSRQ update as ESPout_CONTROL OE perm on
2023-01-19 Added scope to debug ESP BUSRQ
2023-01-19 Circuit fix, cross connection on 245 Data/Addr OE
2023-01-22 Bus ACk added to ESP interrupt
2023-05-01 document ardunio pins
2023-05-01 Z80 basic IO test added
2023-05-01 ESP run slow down and selerate SPI RX method
2023-05-01 refactoring ESP_ROM_Test
2023-05-03 Fixed bus conflict ESPout_Data OE only on WR
2023-05-08 KiCad reference design
2023-05-09 Last KiCad5 commit
2023-05-09 KiCad PCB layout for freerouting test
2023-05-09 Single PCB layout experiements
2023-05-13 Massive fix to KiCad Labels
2023-05-13 KiCad Labels mostly fixed
2023-05-13 Clean KiCad7 folder
2023-05-14 KiCAD attempt to route a single board (failed)
2023-05-14 KiCad massive refactoring to enable modular PCB design
2023-05-16 Unpicked CoreLogic Buses, some symbol updates
2023-05-17 KiCAD Fully expanded Logic core connector
2023-05-17 KiCad forgot to fix the path on connector schem
2023-05-17 KiCad symbol library changes on logic core
2023-05-17 KiCad experiment with logic core PCB
2023-05-17 KiCad diode OR gate example added to Core
2023-05-17 Archiving old KiCAD 5 version
2023-05-17 KiCAD fixed ESP Wrover Library references
2023-05-17 KiCad repairing grid alignment
2023-05-17 KiCAD - grid alignment errors fixed
2023-05-17 Kicad Symbols error fixes and ERC bug fixes
2023-05-18 KiCad - ALMOST ERROR FREE!!!!
2023-05-18 KiCad - mainly added TODO notes this morning
2023-05-18 KiCad - Library fixes and AS6C1008 memory added
2023-05-19 KiCad - Swapped out RIO and CACHE symbols
2023-05-19 KiCad - last 5 errors
2023-05-19 KiCAD PCB layout testing
2023-05-20 KiCad close but failed attempt at PCB
2023-05-20 KiCAD - PSU LED fix
2023-05-20 KiCad - Fixed Hardlock SET/RESET issue on ERC
2023-05-20 KiCad - Refactoring RIO IOCACHE to projects
2023-05-20 KiCad - Refactor Z80_BUS to Z80-BUS_ZXspectrum48K
2023-05-20 KiCad - Refactored Logic core to GLUE
2023-05-20 KiCad - Refactored the SPI bus
2023-05-20 KiCad - Proof of concept PCB in-progress
2023-05-21 KiCad Prototype routing (failed)
2023-05-21 KiCad - First prototype routed
2023-05-21 KiCad - files for fabricating
2023-05-28 Reorganised the project again
2023-05-31 Documentation update
2023-05-31 Readme corrections
2023-05-31 Fixed a bug A11 A10 mixed up on CACHE IC
2023-05-31 exclude KiCad backup files
2023-05-31 Track space calculator
2023-05-31 Fixed all the pathing issues in the projects. Added documentation and _impl project in each module to create PCBs
2023-06-01 CORE_ESP32-WROVER_impl added
2023-06-01 GLUE is broken again, logic gate annotation issue
2023-06-01 KiCad FIXED GLUE
2023-06-01 KiCad GLUE PCB routed
2023-06-01 KiCad IOCACHE_impl
2023-06-01 KiCad RIO impl
2023-06-01 KiCad Origins for gerbers
2023-06-01 Narrow versions of RIO CACHE
2023-06-02 KiCad Attempted Concept design
2023-06-02 KiCad ZXspectrum concept
2023-06-02 KiCad Another attempt to route concept adapter
2023-06-02 Kicad concept adapter still wont route
2023-06-03 KiCad Cleaned up SPI schem
2023-06-03 KiCad - SPI bus impl
2023-06-03 KiCad Revision 2 of zxspectrum concept adapter
2023-06-03 KICad fixed SPI impl
2023-06-03 KiCad Adapter Concept v2 pcb draft layout
2023-06-03 KiCad adapter concept v2 for routing
2023-06-04 KiCad Freerouting worked on concept adapter v2
2023-06-04 KiCad Routing applied to concept adapter PCB
2023-06-04 KiCad Removed PCB files from the modules
2023-06-04 KiCad - Gerber and drill exports, pre-fab prep
2023-06-04 Fabrication setup for pcb2gcode
2023-06-04 KiCad Corrected the orientation of the impl PCBs
2023-06-04 Prepared gcode for IOCACHE
2023-06-04 pcb2gcode corrected tool change possition settings
2023-06-04 pcb2gcode corrected milling spindle speed
2023-06-06 KiCad about ready to try make an IOCACHE
2023-06-06 Pcb2Gcode RIO prepared for fabrication
2023-06-07 pcb2gcode updates zsafe drill depth cut feed speed
2023-06-09 pcb2gcode updates to script slowed miling rate
2023-06-16 pcb2gcode add waypoint comments to gcode
2023-06-16 Fabrication updates (gcode)
2023-06-16 pcb2gcode new cutting settings, svgs moved 2 gcode
2023-06-16 removing duplicate
2023-06-19 SimulIDE Started new simulation
2023-06-19 pcb2gcode cutting operation changed (slower)
2023-06-19 Simulide New simulation of the circuit diagrams
2023-06-20 simulide fixed Z80 rom access
2023-06-23 Fixed RIOconfig control patterns
2023-06-23 Code Refactored method names
2023-06-23 Code work through ESP CACHE access
2023-06-25 Code : no ESPLock needed when using Z80 BUSRQ
2023-06-25 Fixed CACHE and SPI bugs
2023-06-26 code comments
2023-06-27 KICAD IOCACHE fixed
2023-06-27 KiCad - Fixed GLUE (need to update concept v2)
2023-06-27 KiCad SPI fixed
2023-06-28 KiCad Conceptv2 broken dont use yet!
2023-07-01 CODE RIO IOd access
2023-07-01 SIMULIDE house keeping
2023-07-01 Fixing everything with ThatOldNerd!
2023-07-01 SimulIDE cleaned up removed unrequired parts
2023-07-01 Code : massive refactor and fixing of Z80 emu side
2023-07-03 Code Refactored ESP side of things
2023-07-03 CODE ESP access RIO ROM
2023-07-04 CODE bug in the BUSRQ ISR
2023-07-04 FIXED THE SPI BUS (stable)
2023-07-04 Cleaned up the ESP (spi) bus idle
2023-07-04 CODE RIO ROM Z80 ESP passing
2023-07-04 Console debug added, ESP RIO tests passing
2023-07-04 CODE ESP Cache Status and Data test passing
2023-07-04 CODE ESP fill Cache status test working
2023-07-04 CODE z80 Cache debugging
2023-07-20 Simulation - SPI updates code and corrections
2023-07-25 CODE & SIM Applied the SPI clock fix to 165s
2023-07-25 SIM Removed transistor inverter
2023-07-30 SIM - Renamed to make clear lead version
2023-07-30 KICAD - Restructure and SPI version2 Draft
2023-07-30 KICAD - RIO Impl update
2023-07-30 KICAD IOCACHE update
2023-07-30 KICAD - SPI_V2 board implementation
2023-08-06 Shorten folder names
2023-08-06 ignoring CNC files path too long for windows
2023-08-23 KICAD: Updates to base achemtics for GLUE
2023-08-23 SIMULIDE: Update to the simulation for GLUE fixes
2023-08-25 KICAD: Setup for recreating concept adapter
2023-10-03 ThatOldNerds V2 of the concept design.
2023-11-17 Fixed to the Simulation and Test Code
2023-11-17 Fixed rectangle layers
2023-11-18 FIX SPI CE signalling added
2023-11-18 RIO ROM test improvements
2023-11-18 ROM test error message update
2023-11-19 added methods for write read testing
2023-11-19 Fixed ESP_SPI_INT_CE start up LOW
2023-11-19 Changed ESP hardlock, bus IDLE, getLocalBus
2023-11-19 More simulation fix proposals (RIO decoder)
2023-11-19 SIM Corrected SPI control Bias wired wrong
2023-11-19 ESP Local Bus protocol updates
2023-11-19 Comment on the Local SPI signalling
2023-11-19 Refactored for clarity
2023-11-19 Bus Idle call removed - implicit SPI output off
2023-11-19 Fancy ESP test reporting
2023-11-20 CacheData Test update
2023-11-20 ROMCS override internal ROM cant be done from SPI
2023-11-20 RIO IOD Config Access correction
2023-11-20 ESP RIO Config access test update
2023-11-20 Full set of ESP RIO and CACHE tests
2023-11-21 Added diagrams of ADDRESS BUS
2023-11-22 Host reset function added
2023-11-22 Code working, but loop back on start up SPI BUSRQ
2023-11-23 Mark start and end of test loop
2023-11-23 Test RIOs first 255 addresses
2023-11-23 Diagram updates
2023-11-25 Clean up console output
2023-11-25 Double send SPI on setup for Simulator bug
2023-11-25 SIM Update to design
2023-11-25 Enable all tests
2023-11-26 SIM update on texted fix
2023-11-27 SIM Minor refactoring
